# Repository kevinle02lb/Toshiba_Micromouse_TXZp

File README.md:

<div align="center">

# 🐭 Toshiba Micromouse

**Autonomous 16×16 Maze-Solving Robot**  
*Register-level firmware on Arm Cortex-M4*

</div>

---

## Overview

Micromouse is a classic robotics competition: an autonomous palm-sized robot explores a 16×16 grid maze, maps the walls, solves for the center, and then races back through the fastest route it discovered.

This project implements the entire stack from scratch — custom 4-layer PCB, mechanical chassis, and register-level firmware — with no reliance on external HAL libraries.

---

## Platform

<div align="center">

### **Toshiba TMPM4KNF10AFG** — Arm Cortex-M4 with FPU

</div>

The TMPM4KNF10AFG comes from the **[M4K Group](https://toshiba.semicon-storage.com/us/semiconductor/product/microcontrollers/txz4aplus-series/m4k-group.html)** of Toshiba's **[TXZ+™4A Series](https://toshiba.semicon-storage.com/us/semiconductor/product/microcontrollers/txz4aplus-series.html)** — 160 MHz Arm Cortex-M4 microcontrollers built for motor and inverter control. It pairs a fast floating-point core with dedicated on-chip hardware for driving motors, reading encoders, and sampling analog sensors, and is used across industrial and consumer motion systems such as BLDC/PMSM drives, HVAC compressors, power tools, and factory automation — with IEC 60730 self-diagnosis support for appliance functional safety.

| Capability | Role in this build |
|-----------|--------------------|
| Cortex-M4 @ 160 MHz + FPU | Navigation, PID, and flood-fill maze solving |
| On-chip motor & encoder hardware | Wheel feedback and PPG-generated motor PWM |
| High-speed analog sensing | IR wall detection |

The same silicon built for industrial three-phase drives runs a smaller-scale problem here — a 1 kHz closed-loop PID over two brushed DC gear-motors — with dedicated hardware handling encoder counting and motor PWM so the CPU stays free for navigation and flood-fill maze solving.

---

## Built With

<div align="center">

|  |  |  |  |  |
|:---:|:---:|:---:|:---:|:---:|
| **Arm Cortex-M4** | **Keil µVision** | **KiCad** | **Fusion 360** | **Git** |
| Register-level C | IDE / Build / Flash | 4-layer PCB | Chassis CAD | Version Control |

</div>

---

## Architecture Highlights

- **Flood-fill maze solver** — pure logic, zero hardware coupling
- **1 kHz per-wheel PID** speed control
- **Fully hand-written HAL** from datasheets, no external libraries
- **Relative-move navigation** — turn error never compounds across a run
- **Custom 4-layer PCB** with integrated motor drivers & IR sensors

---

## Gallery

<div align="center">

 &nbsp;&nbsp; 

*Custom PCB and test maze run*

<br>

*Fusion 360 render of the full mechanical assembly*

</div>

---

## Documentation
 
| Path | Contents |
|------|----------|
| [`src/README.md`](src/README.md) | Firmware architecture, control loops, pin map, timer config |
| [`pcb/README.md`](pcb/README.md) | Board specs, layout, schematic, component list |
| [`docs/README.md`](docs/README.md) | Docs index — assets, evidence, and analysis tooling |
| [`docs/evidence/README.md`](docs/evidence/README.md) | Module-test checklist and captured evidence |

---

## Quick Start

```text
IDE:     Keil µVision
Target:  TMPM4KNF10AFG (Arm Cortex-M4)
Debug:   CMSIS-DAP
Flash:   512 KB on-chip
```

---

<div align="center">

**Kevin Le** &nbsp;•&nbsp; 2026 &nbsp;•&nbsp;
</div>

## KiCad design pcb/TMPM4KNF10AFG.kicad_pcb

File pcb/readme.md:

<div align="center">

# Micromouse PCB

**Custom 4-Layer Control Board**  
*Integrated MCU, motor drivers, and IR sensing*

</div>

---

## Overview

The mainboard is a custom 4-layer PCB designed in KiCad that carries the full electronics stack on a single micromouse-sized board: the microcontroller, dual motor drivers, four IR wall sensors, and the power and debug interface.

---

## Board Specs

| Spec | Detail |
|------|--------|
| Layers | 4-layer |
| MCU | Toshiba TMPM4KNF10AFG (Cortex-M4F) |
| Motor drivers | 2 × TB67H450AFNG H-bridge |
| Sensing | 4 × IR emitter / receiver pairs |
| Debug | CMSIS-DAP (SWD) via TXB0104 level shifter |
| Supply | 5 V |

---

## Layout

<div align="center">

*Copper layers and component placement*

</div>

---

## Key Components

| Component | Part | Role |
|-----------|------|------|
| MCU | TMPM4KNF10AFG | Cortex-M4F — control & sensing |
| Motor driver | TB67H450AFNG ×2 | Brushed DC H-bridge, PWM speed control |
| Motors | Pololu #5211 N20 30:1 | Drive, with quadrature encoders |
| IR sensing | IR LED + phototransistor ×4 | Wall detection via ADC |
| Level shifter | TXB0104 | 5 V ↔ 3.3 V for SWD debug |

---

## Schematic

The full schematic is available as a PDF:

[View schematic (PDF)](Schematic.pdf)

---

## Files

| File | Contents |
|------|----------|
| `*.kicad_sch` | Schematic source |
| `*.kicad_pcb` | Board layout source |
| `gerbers/` | Fabrication outputs |

---

<div align="center">

[← Back to main README](../README.md)

</div>

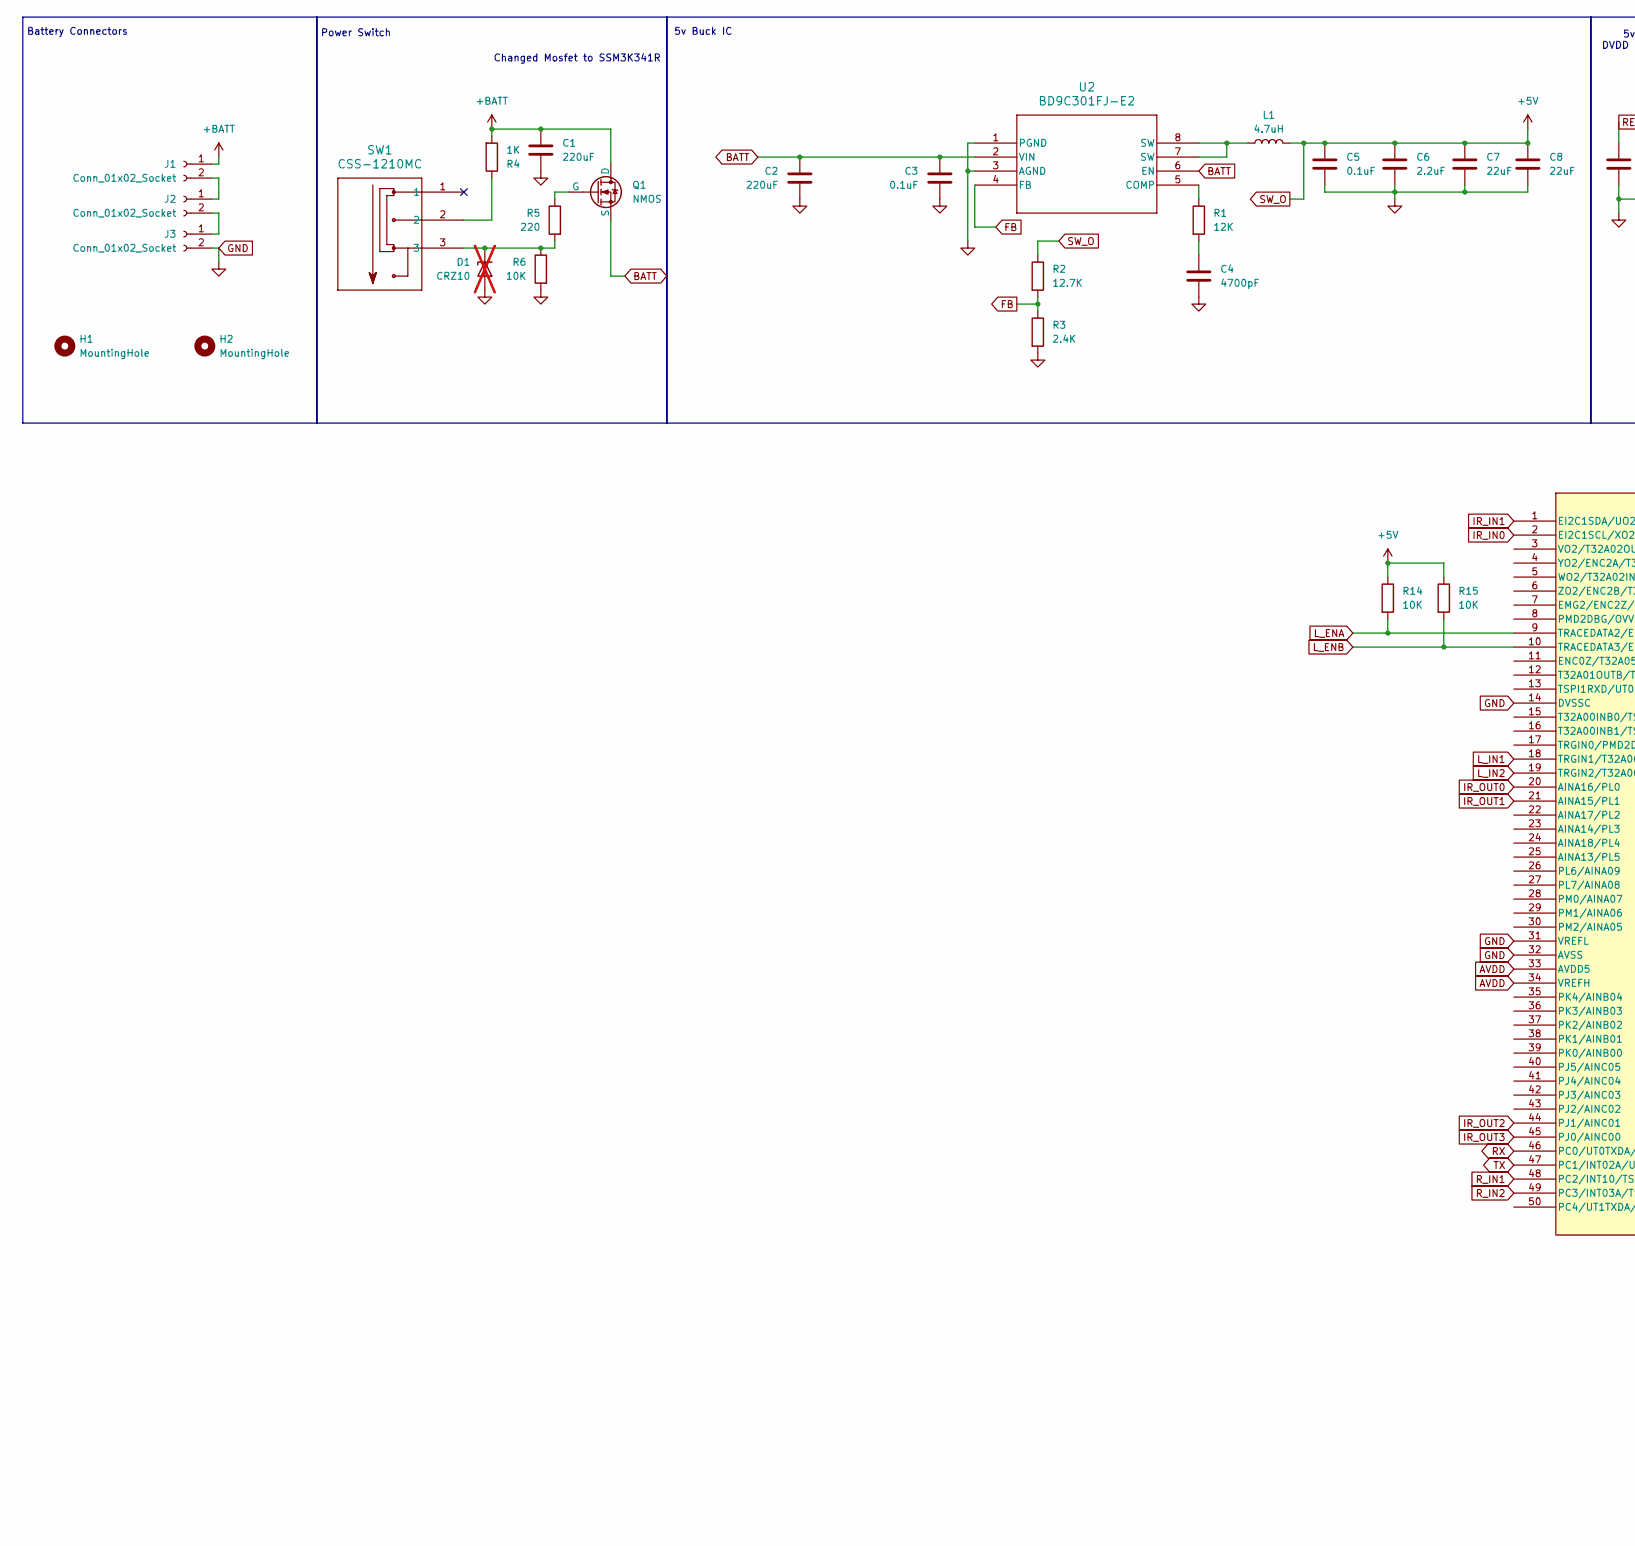
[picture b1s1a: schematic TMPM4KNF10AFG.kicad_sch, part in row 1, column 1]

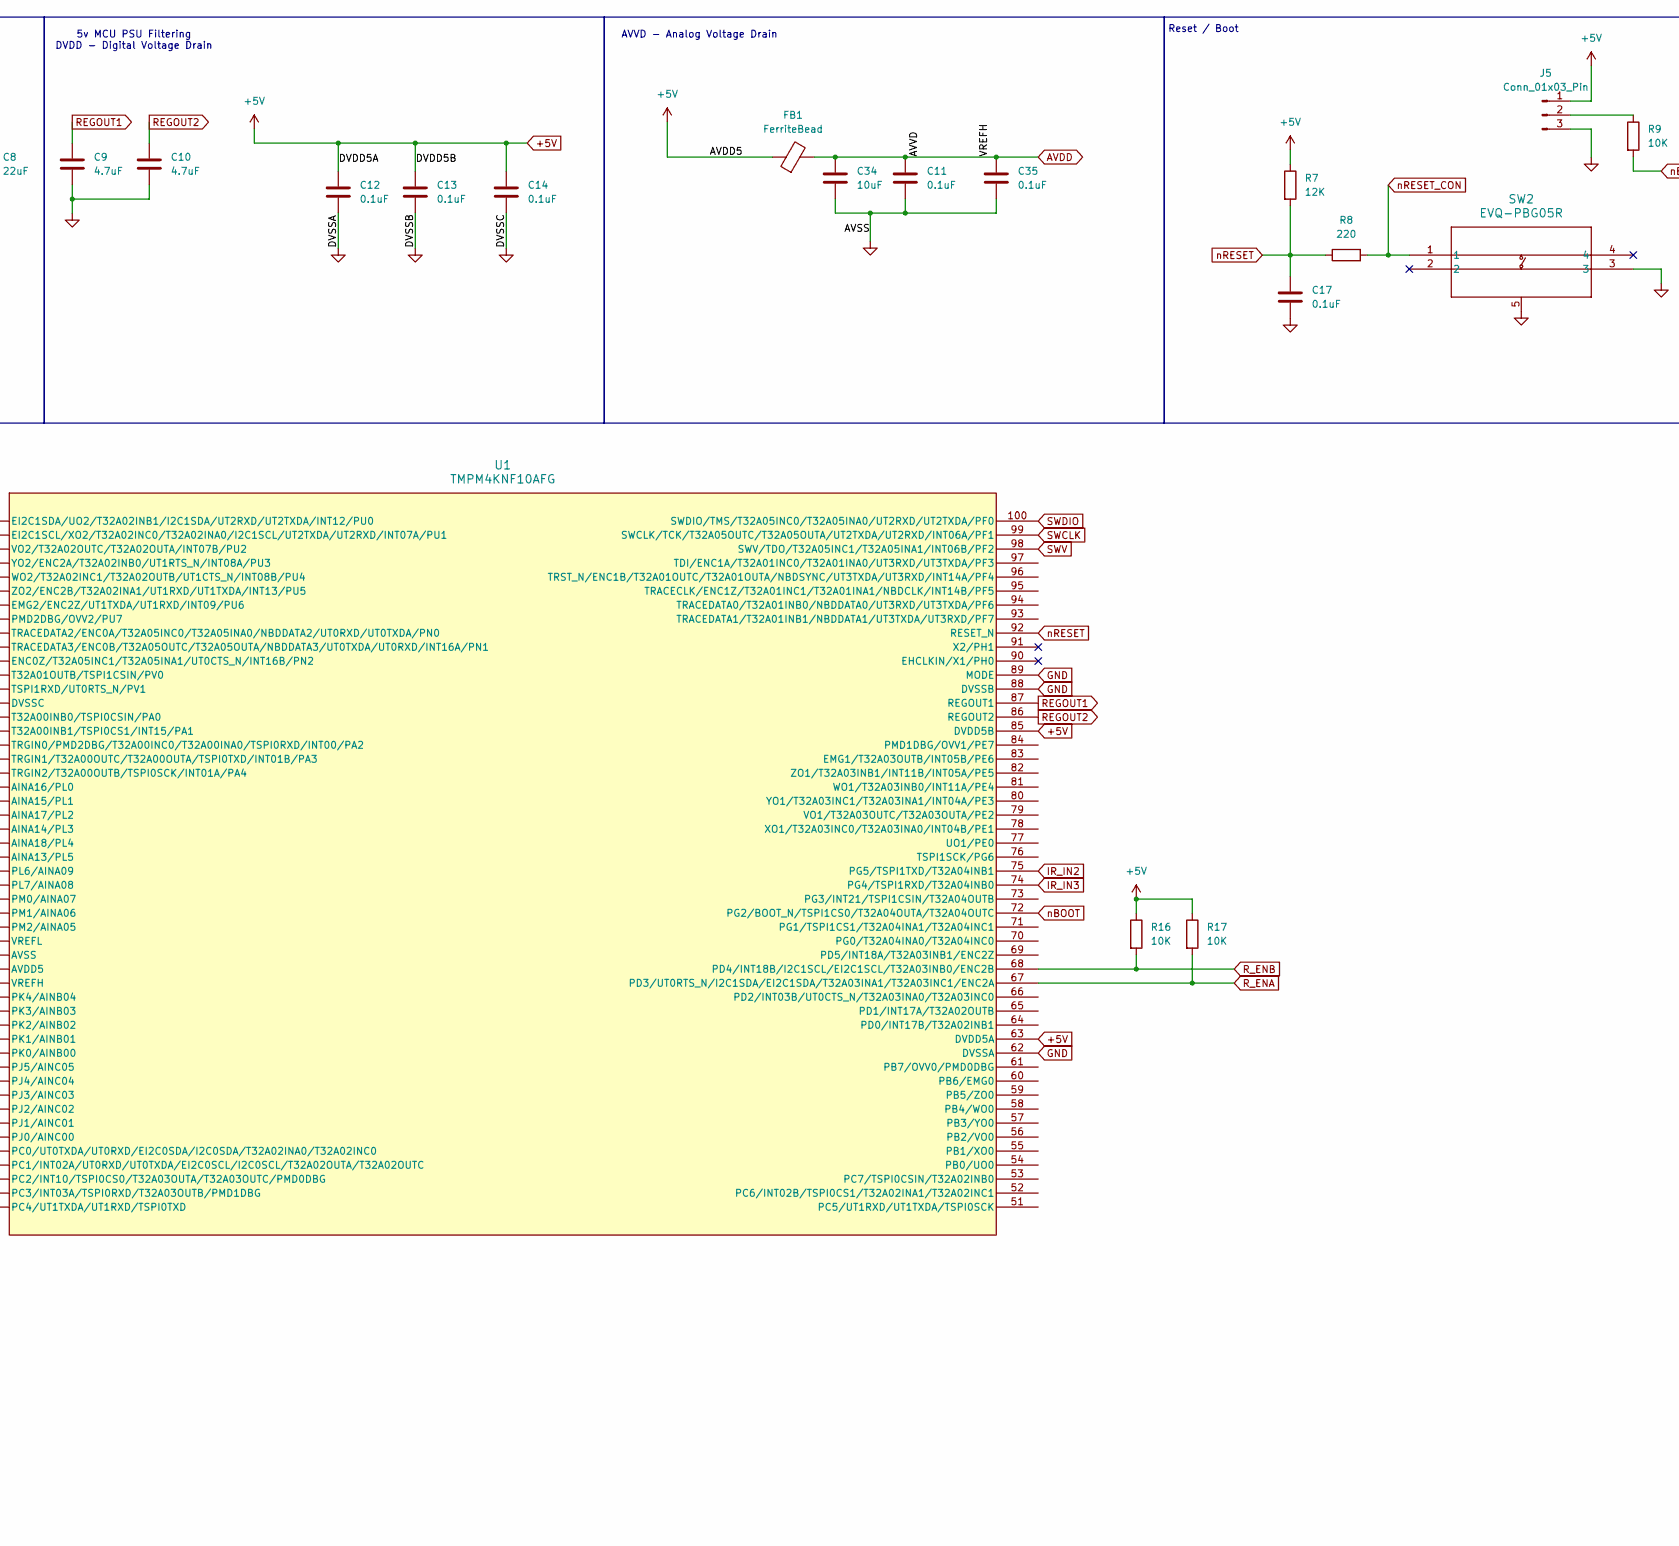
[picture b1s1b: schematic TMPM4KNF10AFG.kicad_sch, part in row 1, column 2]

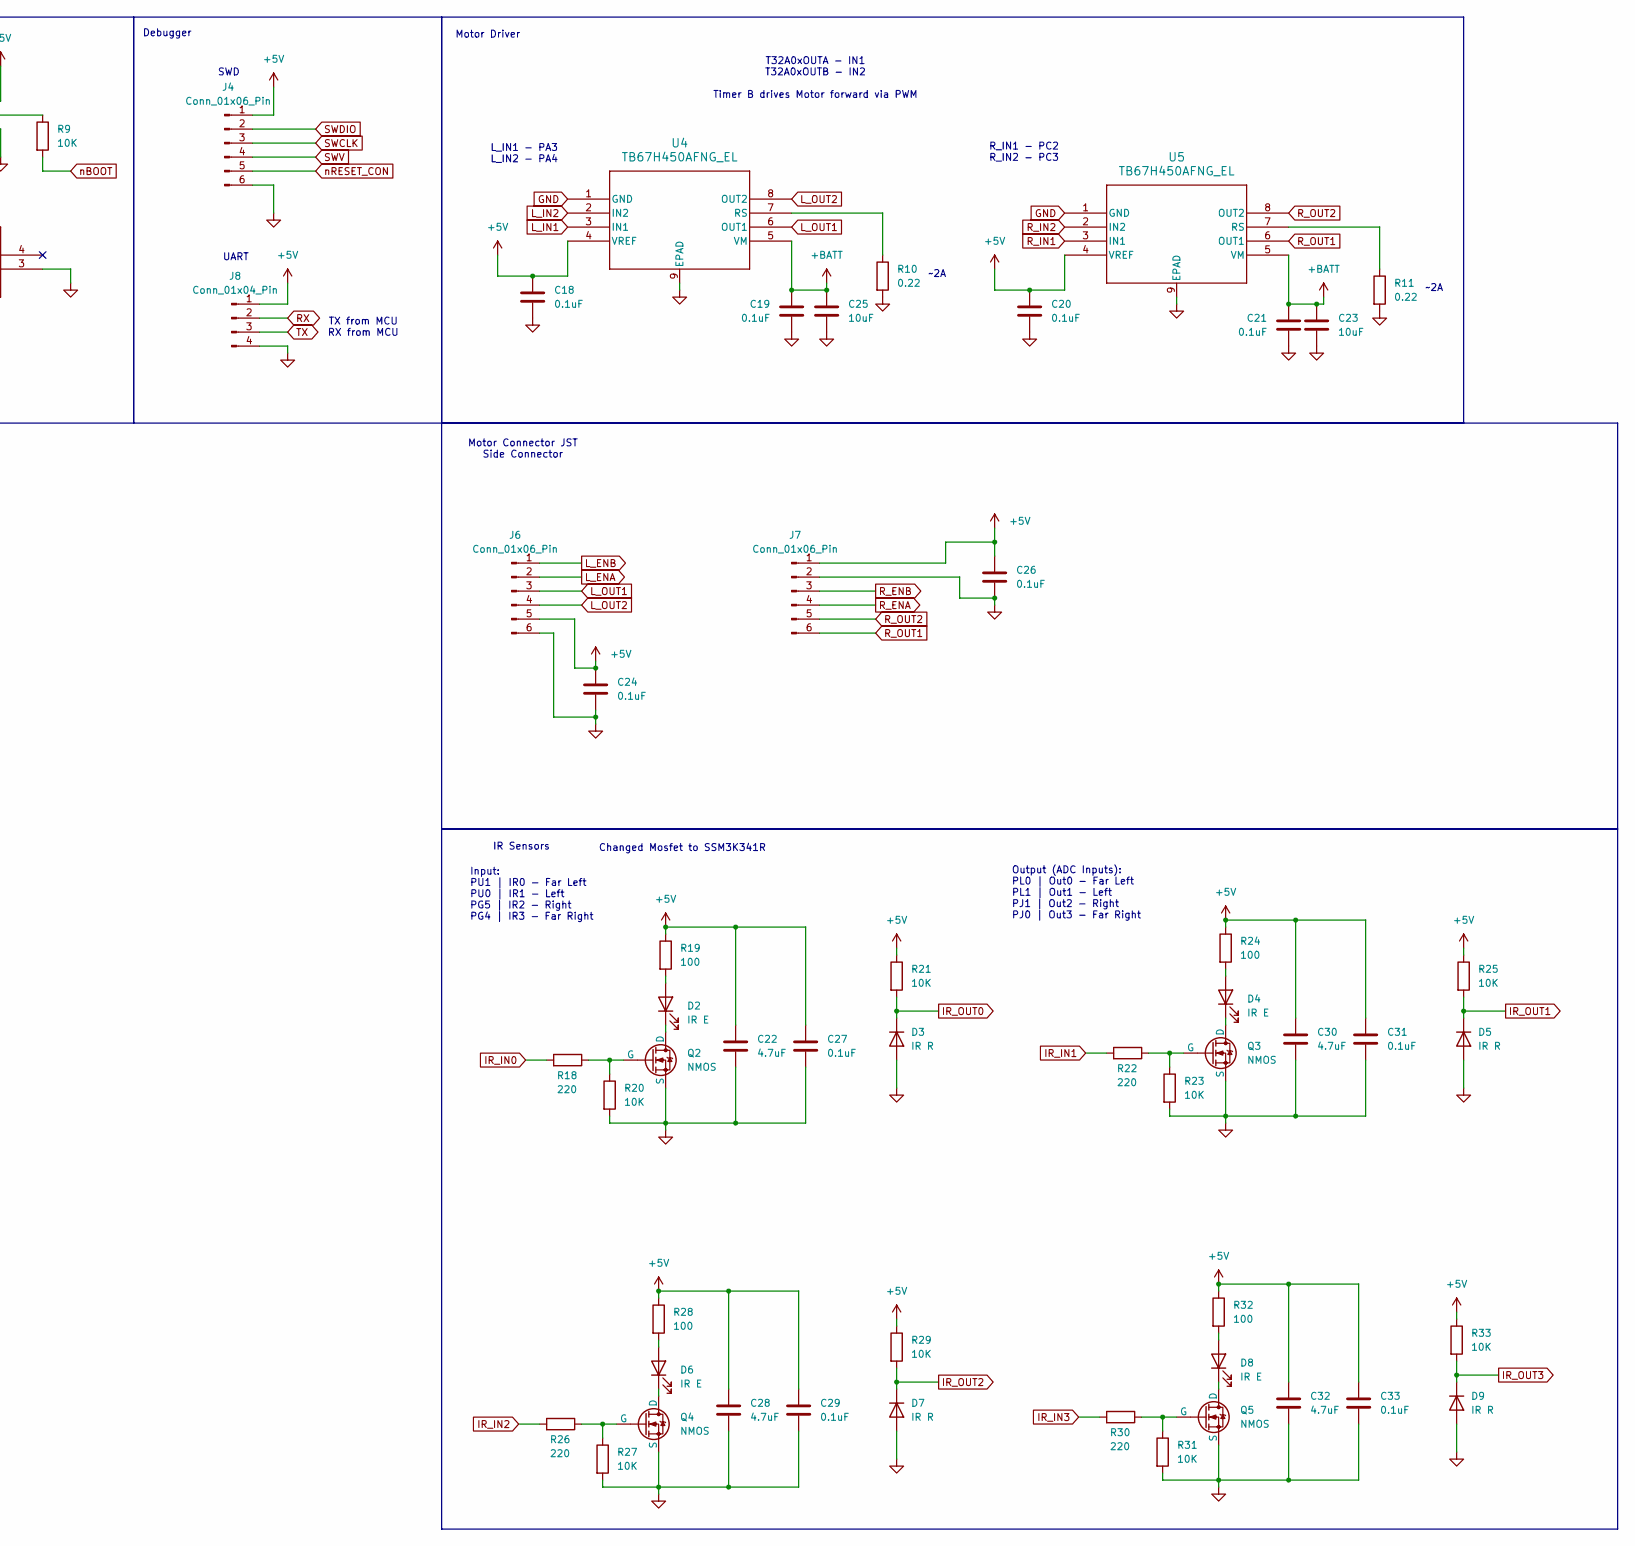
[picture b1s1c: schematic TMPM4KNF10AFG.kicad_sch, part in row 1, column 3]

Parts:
C1, C2: 220uF; CAP_20SVPG220M
C3, C5, C11, C12, C13, C14, C17, C18, C19, C20, C21, C24, C26, C27, C29, C31, C33, C35: 0.1uF; C_0805_2012Metric_Pad1.18x1.45mm_HandSolder
C4: 4700pF; C_0805_2012Metric_Pad1.18x1.45mm_HandSolder
C6: 2.2uF; C_0805_2012Metric_Pad1.18x1.45mm_HandSolder
C7, C8: 22uF; C_0805_2012Metric_Pad1.18x1.45mm_HandSolder
C9, C10, C22, C28, C30, C32: 4.7uF; C_0805_2012Metric_Pad1.18x1.45mm_HandSolder
C23, C25, C34: 10uF; C_0805_2012Metric_Pad1.18x1.45mm_HandSolder
D1: CRZ10; D_SOD-123F; not fitted
D2, D4, D6, D8: IR E; LED_D5.0mm_Horizontal_O1.27mm_Z3.0mm_Clear
D3, D5, D7, D9: IR R; LED_D5.0mm_Horizontal_O1.27mm_Z3.0mm_IRBlack
FB1: FerriteBead; L_0805_2012Metric_Pad1.05x1.20mm_HandSolder
H1, H2: MountingHole; MountingHole_3.2mm_M3
J1, J2, J3: Conn_01x02_Socket; JST_PH_S2B-PH-K_1x02_P2.00mm_Horizontal
J4: Conn_01x06_Pin; PinHeader_1x06_P2.54mm_Vertical
J5: Conn_01x03_Pin; PinHeader_1x03_P2.54mm_Vertical
J6, J7: Conn_01x06_Pin; PAD_01x06_2.54mm
J8: Conn_01x04_Pin; PinHeader_1x04_P2.54mm_Vertical
L1: 4.7uH; IND_1217AS-H-4R7N=P3
Q1, Q2, Q3, Q4, Q5: NMOS; SOT-23F_TOS-M
R1, R7: 12K; R_0805_2012Metric_Pad1.20x1.40mm_HandSolder
R2: 12.7K; R_0805_2012Metric_Pad1.20x1.40mm_HandSolder
R3: 2.4K; R_0805_2012Metric_Pad1.20x1.40mm_HandSolder
R4: 1K; R_0805_2012Metric_Pad1.20x1.40mm_HandSolder
R5, R8, R18, R22, R26, R30: 220; R_0805_2012Metric_Pad1.20x1.40mm_HandSolder
R6, R9, R14, R15, R16, R17, R20, R21, R23, R25, R27, R29, R31, R33: 10K; R_0805_2012Metric_Pad1.20x1.40mm_HandSolder
R10, R11: 0.22; R_0805_2012Metric_Pad1.20x1.40mm_HandSolder
R19, R24, R28, R32: 100; R_0805_2012Metric_Pad1.20x1.40mm_HandSolder
SW1: CSS-1210MC; SW3_CSS-1210MC_NDC
SW2: EVQ-PBG05R; EVQ-PBG05R_PAN
U1: TMPM4KNF10AFG; P-LQFP100-1414-0p50-002_TOS
U2: BD9C301FJ-E2; SOP-J8_ROM
U4, U5: TB67H450AFNG_EL; P-HSOP8-0405-1.27-002_TOS

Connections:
+5V: C5.1, C6.1, C7.1, C8.1, C12.1, C13.1, C14.1, C18.1, C20.1, C22.1, C24.1, C26.1, C27.1, C28.1, C29.1, C30.1, C31.1, C32.1, C33.1, FB1.1, J4.1, J5.1, J6.5, J7.1, J8.1, L1.2, R2.1, R7.1, R14.1, R15.1, R16.1, R17.1, R19.1, R21.1, R24.1, R25.1, R28.1, R29.1, R32.1, R33.1, U1.63 (DVDD5A), U1.85 (DVDD5B), U4.4 (VREF), U5.4 (VREF)
+BATT: C1.1, C19.1, C21.1, C23.1, C25.1, J1.1, Q1.1 (D), R4.2, U4.5 (VM), U5.5 (VM)
AVDD: C11.1, C34.1, C35.1, FB1.2, U1.33 (AVDD5), U1.34 (VREFH)
BATT: C2.1, C3.1, Q1.3 (S), U2.2 (VIN), U2.6 (EN)
FB: R2.2, R3.1, U2.4 (FB)
GND: C1.2, C2.2, C3.2, C4.2, C5.2, C6.2, C7.2, C8.2, C9.2, C10.2, C11.2, C12.2, C13.2, C14.2, C17.2, C18.2, C19.2, C20.2, C21.2, C22.2, C23.2, C24.2, C25.2, C26.2, C27.2, C28.2, C29.2, C30.2, C31.2, C32.2, C33.2, C34.2, C35.2, D1.2 (A), D3.2 (A), D5.2 (A), D7.2 (A), D9.2 (A), J3.2, J4.6, J5.3, J6.6, J7.2, J8.4, Q2.3 (S), Q3.3 (S), Q4.3 (S), Q5.3 (S), R3.2, R6.2, R10.2, R11.2, R20.2, R23.2, R27.2, R31.2, SW2.3, SW2.5, U1.14 (DVSSC), U1.31 (VREFL), U1.32 (AVSS), U1.62 (DVSSA), U1.88 (DVSSB), U1.89 (MODE), U2.1 (PGND), U2.3 (AGND), U4.1 (GND), U4.9 (EPAD), U5.1 (GND), U5.9 (EPAD)
IR_IN0: R18.2, U1.2 (EI2C1SCL/XO2/T32A02INC0/T32A02INA0/I2C1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)
IR_IN1: R22.2, U1.1 (EI2C1SDA/UO2/T32A02INB1/I2C1SDA/UT2RXD/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)
IR_IN2: R26.2, U1.75 (PG5/TSPI1TXD/T32A04INB1)
IR_IN3: R30.2, U1.74 (PG4/TSPI1RXD/T32A04INB0)
IR_OUT0: D3.1 (K), R21.2, U1.20 (AINA16/PL0)
IR_OUT1: D5.1 (K), R25.2, U1.21 (AINA15/PL1)
IR_OUT2: D7.1 (K), R29.2, U1.44 (PJ1/AINC01)
IR_OUT3: D9.1 (K), R33.2, U1.45 (PJ0/AINC00)
L_ENA: J6.2, R14.2, U1.9 (TRACEDATA2/ENC0A/T32A05INC0/T32A05INA0/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)
L_ENB: J6.1, R15.2, U1.10 (TRACEDATA3/ENC0B/T32A05OUTC/T32A05OUTA/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)
L_IN1: U1.18 (TRGIN1/T32A00OUTC/T32A00OUTA/TSPI0TXD/I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), U4.3 (IN1)
L_IN2: U1.19 (TRGIN2/T32A00OUTB/TSPI0SCK/INT01A/PA4), U4.2 (IN2)
L_OUT1: J6.3, U4.6 (OUT1)
L_OUT2: J6.4, U4.8 (OUT2)
unnamed: C4.1, R1.2
unnamed: D1.1 (K), R5.2, R6.1, SW1.3
unnamed: D2.2 (A), R19.2
unnamed: D2.1 (K), Q2.1 (D)
unnamed: D4.2 (A), R24.2
unnamed: D4.1 (K), Q3.1 (D)
unnamed: D6.2 (A), R28.2
unnamed: D6.1 (K), Q4.1 (D)
unnamed: D8.2 (A), R32.2
unnamed: D8.1 (K), Q5.1 (D)
unnamed: J1.2, J2.1
unnamed: J2.2, J3.1
unnamed: J5.2, R9.1
unnamed: L1.1, U2.7 (SW), U2.8 (SW)
unnamed: Q1.2 (G), R5.1
unnamed: Q2.2 (G), R18.1, R20.1
unnamed: Q3.2 (G), R22.1, R23.1
unnamed: Q4.2 (G), R26.1, R27.1
unnamed: Q5.2 (G), R30.1, R31.1
unnamed: R4.1, SW1.2
unnamed: R1.1, U2.5 (COMP)
unnamed: R10.1, U4.7 (RS)
unnamed: R11.1, U5.7 (RS)
REGOUT1: C9.1, U1.87 (REGOUT1)
REGOUT2: C10.1, U1.86 (REGOUT2)
RX: J8.2, U1.46 (PC0/UT0TXDA/UT0RXD/EI2C0SDA/I2C0SDA/T32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)
R_ENA: J7.4, R17.2, U1.67 (PD3/UT0RTS_N/I2C1SDA/EI2C1SDA/T32A03INA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)
R_ENB: J7.3, R16.2, U1.68 (PD4/INT18B/I2C1SCL/EI2C1SCL/T32A03INB0/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)
R_IN1: U1.48 (PC2/INT10/TSPI0CS0/T32A03OUTA/T32A03OUT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), U5.3 (IN1)
R_IN2: U1.49 (PC3/INT03A/TSPI0RXD/T32A03OUTB/PMD1DBG), U5.2 (IN2)
R_OUT1: J7.6, U5.6 (OUT1)
R_OUT2: J7.5, U5.8 (OUT2)
SWCLK: J4.3, U1.99 (SWCLK/TCK/T32A05OUTC/T32A05OUTA/UT2TXDA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)
SWDIO: J4.2, U1.100 (SWDIO/TMS/T32A05INC0/T32A05INA0/UT2RXD/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)
SWV: J4.4, U1.98 (SWV/TDO/T32A05INC1/T32A05INA1/INT06B/PF2)
TX: J8.3, U1.47 (PC1/INT02A/UT0RXD/UT0TXDA/EI2C0SCL/I2C0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)
nBOOT: R9.2, U1.72 (PG2/BOOT_N/TSPI1CS0/T32A04OUTA/T32A04OU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)
nRESET: C17.1, R7.2, R8.1, U1.92 (RESET_N)
nRESET_CON: J4.5, R8.2, SW2.1

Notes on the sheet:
Changed Mosfet to SSM3K341R
Battery Connectors
TX from MCU RX from MCU
R_IN1 - PC2 R_IN2 - PC3
Motor Connector JST Side Connector
UART
Output (ADC Inputs): PL0 | Out0 - Far Left PL1 | Out1 - Left PJ1 | Out2 - Right PJ0 | Out3 - Far Right
5v MCU PSU Filtering DVDD - Digital Voltage Drain
IR Sensors
T32A0xOUTA - IN1 T32A0xOUTB - IN2 Timer B drives Motor forward via PWM
Power Switch
Debugger
5v Buck IC
~2A
L_IN1 - PA3 L_IN2 - PA4
Motor Driver
SWD
AVVD - Analog Voltage Drain
Input: PU1 | IR0 - Far Left PU0 | IR1 - Left PG5 | IR2 - Right PG4 | IR3 - Far Right
Reset / Boot

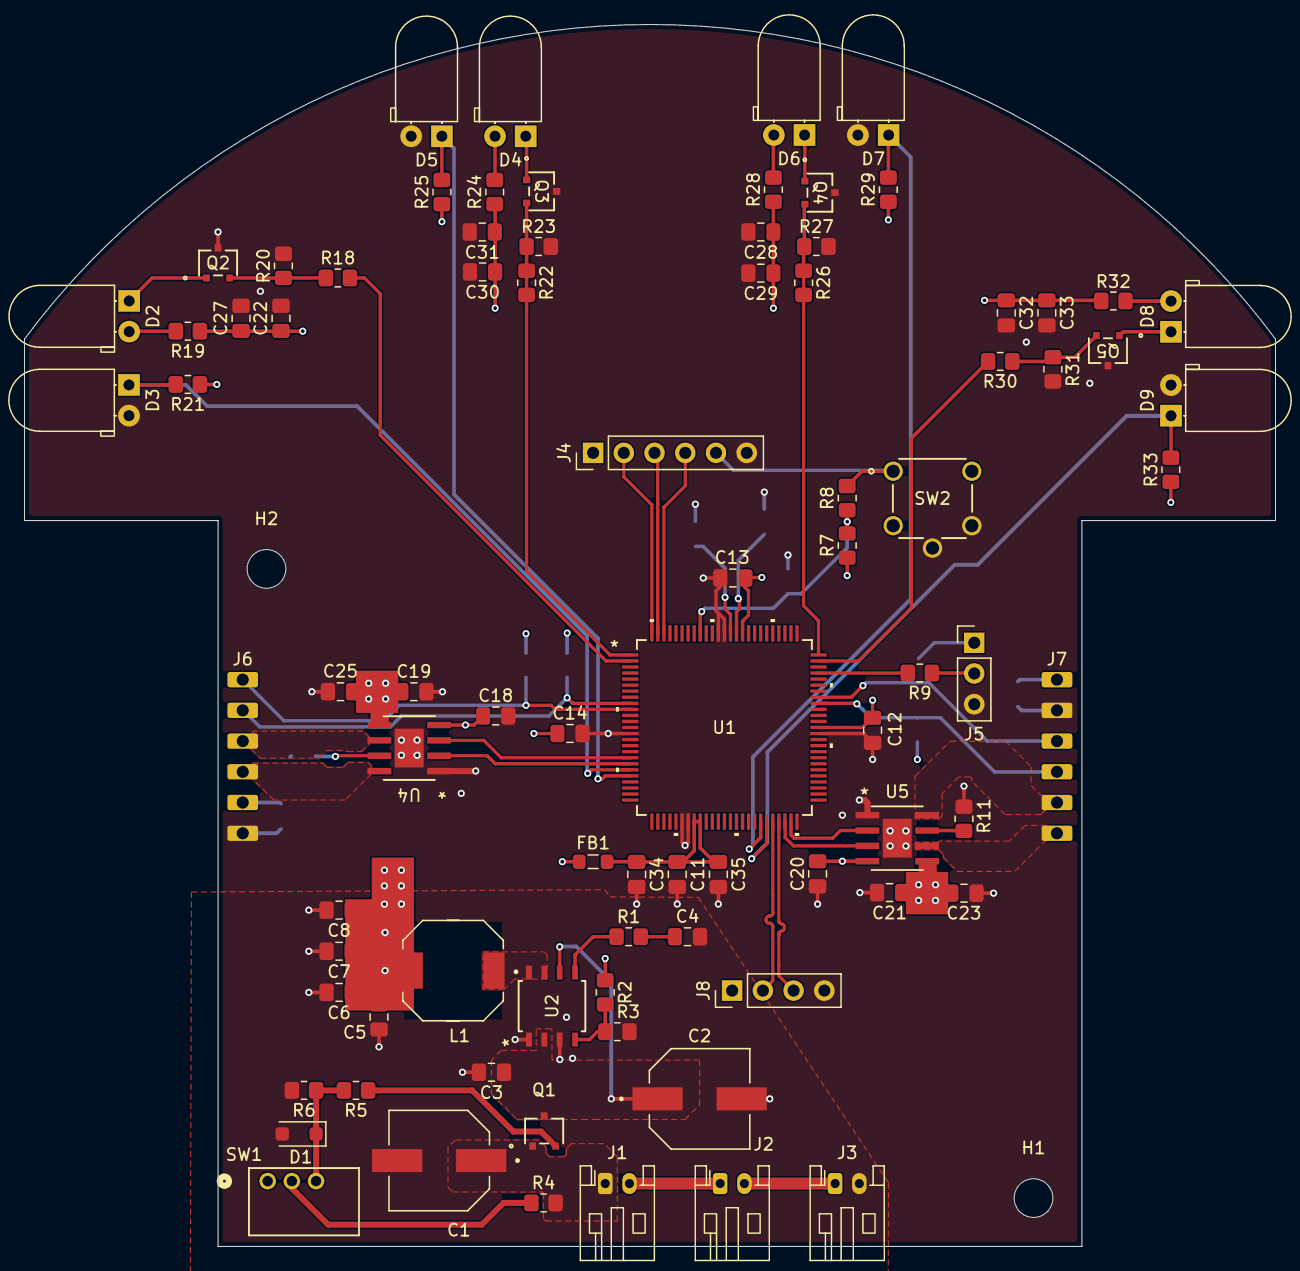
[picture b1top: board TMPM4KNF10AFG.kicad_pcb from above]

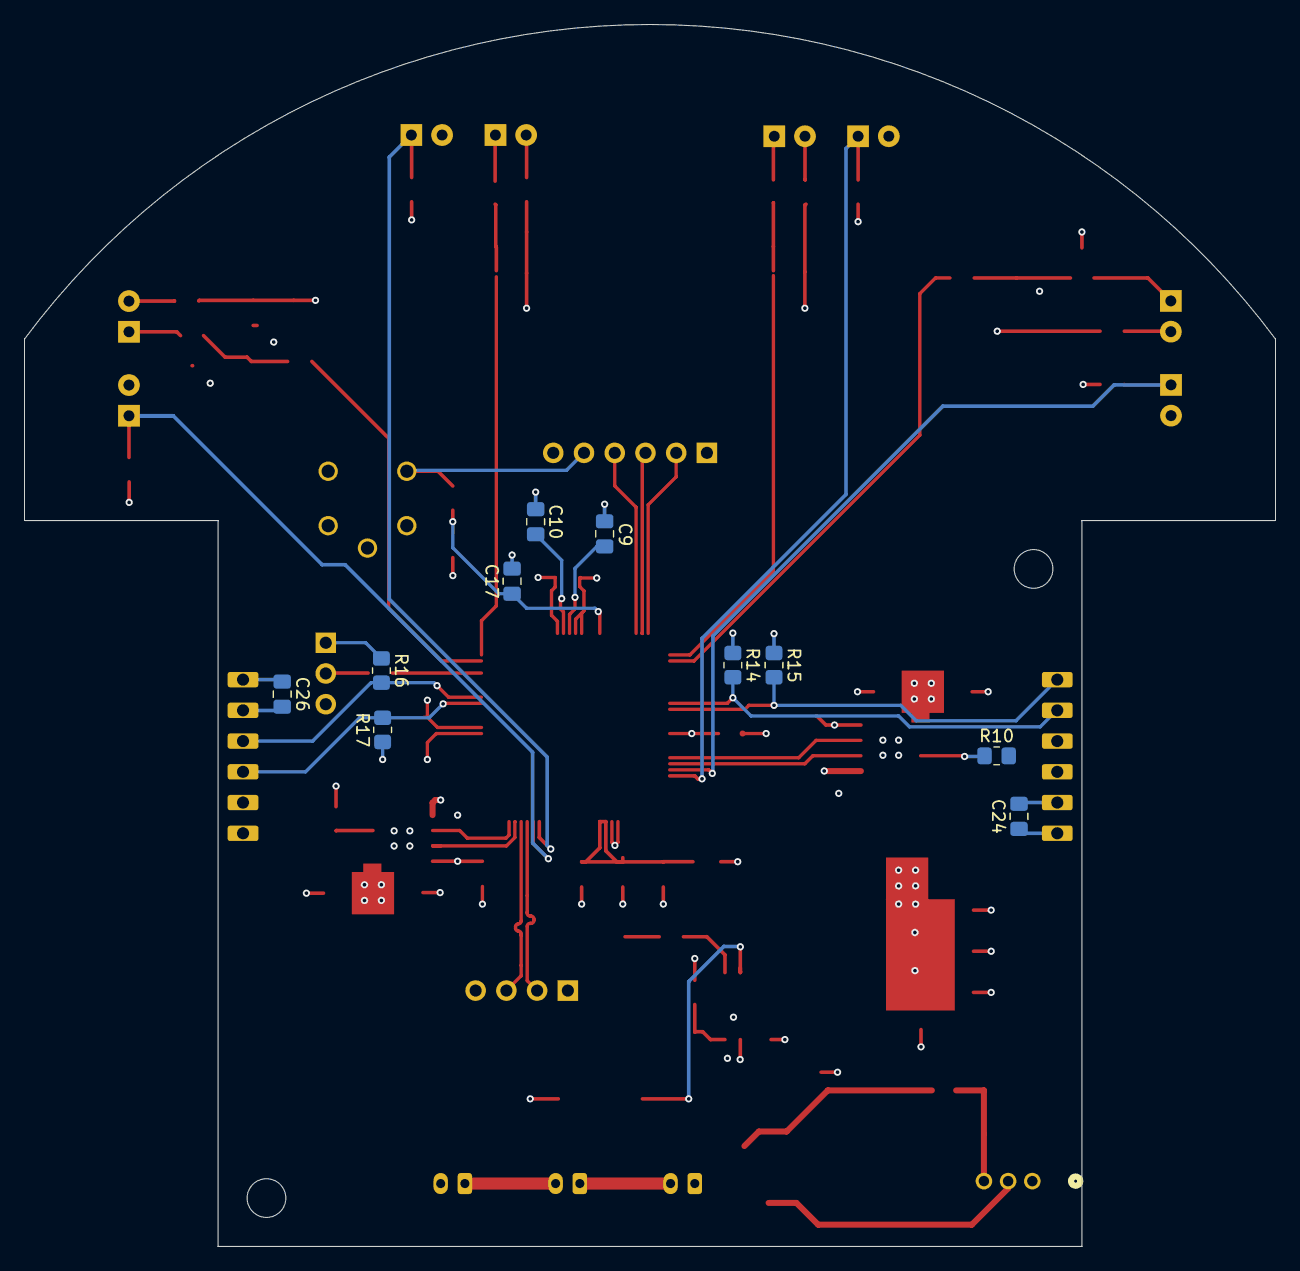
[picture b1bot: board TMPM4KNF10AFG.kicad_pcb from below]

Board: 4 copper layers, 103.4 x 101.0 mm, 96 parts (10 on the bottom side), 59 nets.

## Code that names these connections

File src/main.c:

/**
 ******************************************************************************
 * @file        main.c
 * @brief       Micromouse main firmware entry point
 * @version     V1.0.0
 * @date        05-05-2026
 *
 * @details
 *   Initializes the system clock and all modules, then runs the main control
 *   loop. Every 1 kHz tick (T32A1 interval timer) runs the full pipeline in
 *   fixed order:
 *
 *     Encoder_Update()   -> read quadrature counters, filter wheel speed
 *     Odometry_Update()  -> integrate pose (x, y, heading) from encoders
 *     Motion_Update()    -> PID speed loop, drive motor PWM (ALWAYS runs)
 *     Navigator_Update() -> non-blocking FSM: plan -> turn -> drive -> pause
 *
 *   Navigator is the top-level brain: it calls FloodFill (pure planner) for
 *   the next move, then sequences the physical turn/drive without ever
 *   blocking, so the PID loop above keeps running every tick.
 *
 *   Deployment calibration (must set before real runs):
 *   - IrSensor.c : ir_cal[] table (measured ADC-to-distance points)
 *   - Odometry.h : WHEELBASE_MM (measure wheel-center to wheel-center)
 *   - Encoder    : confirm forward motion yields INCREASING position
 *   - PID.h      : tune gains for CPS-scaled error
 *
 * ___________________________________________________________________________
 * Hardware:
 *   - MCU:     TMPM4KNF10AFG (ARM Cortex-M4, 5V, 160 MHz)
 *   - Motors:  TB67H450AFNG x2 + Pololu #5211 N20 30:1
 *   - Sensors: IR emitter/receiver pairs x4
 *   - Debug:   External CMSIS-DAP w/ Level Shifter (TXB0104)
 *
 * ___________________________________________________________________________
 * Pin Assignment:
 *   ┌─────────────────────────────────────────────────────────────┐
 *   │  PORT A  │ PA3  = 	 T32A00OUTA  (Left PWM IN1)            │
 *   │          │ PA4  = 	 T32A00OUTB  (Left PWM IN2)            │
 *   ├─────────────────────────────────────────────────────────────┤
 *   │  PORT C  │ PC2  = 	 T32A30OUTA  (Right PWM IN1)           │
 *   │          │ PC3  = 	 T32A30OUTB  (Right PWM IN2)           │
 *   ├─────────────────────────────────────────────────────────────┤
 *   │  PORT N  │ PN0  = 	 ENC0A  (Left encoder A)               │
 *   │          │ PN1  = 	 ENC0B  (Left encoder B)               │
 *   ├─────────────────────────────────────────────────────────────┤
 *   │  PORT D  │ PD3  = 	 ENC2A  (Right encoder A)              │
 *   │          │ PD4  = 	 ENC2B  (Right encoder B)              │
 *   ├─────────────────────────────────────────────────────────────┤
 *   │  PORT L  │ PL0  = 	 AINA16  (Far Left IR)                 │
 *   │          │ PL1  = 	 AINA15  (Left IR)                     │
 *   ├─────────────────────────────────────────────────────────────┤
 *   │  PORT J  │ PJ0  =     AINC00  (Far Right IR)                │
 *   │          │ PJ1  = 	 AINC01  (Right IR)                    │
 *   ├─────────────────────────────────────────────────────────────┤
 *   │  PORT U  │ PU0  =     Left IR Emitter                       │
 *   │          │ PU1  =     Far Left IR Emitter                   │
 *   ├─────────────────────────────────────────────────────────────┤
 *   │  PORT G  │ PG4  =     Far Right IR Emitter                  │
 *   │          │ PG5  =     Right IR Emitter                      │
 *   └─────────────────────────────────────────────────────────────┘
 *
 * ___________________________________________________________________________
 * Aliases (for quick reference):
 *   - PA3 = IN1, PA4 = IN2  (Left motor, T32A00OUTA/B)
 *   - PC2 = IN1, PC3 = IN2  (Right motor, T32A30OUTA/B)
 *   - PN0 = ENC0A, PN1 = ENC0B  (Left encoder)
 *   - PD3 = ENC2A, PD4 = ENC2B  (Right encoder)
 *   - PL0 = AINA16 (Far Left IR), PL1 = AINA15 (Left IR)
 *   - PJ1 = AINC01 (Right IR), PJ0 = AINC00 (Far Right IR)
 *   - PU1 = Far Left IR Emitter, PU0 = Left IR Emitter
 *   - PG5 = Right IR Emitter, PG4 = Far Right IR Emitter
 *
 * ___________________________________________________________________________
 * Notes:
 *   - MCU must be powered at 5V for ADC to function.
 *   - See TMPM4KNF10AFG datasheet section 7.2.
 *
 * ___________________________________________________________________________
 * References:
 *   - Product Info:  https://toshiba.semicon-storage.com/info/TXZP-PINFO-M4K(2)_en_20231225.pdf?did=70854
 *   - Datasheet:     https://toshiba.semicon-storage.com/info/TMPM4KNF10AFG_datasheet_en_20250516.pdf?did=155921&prodName=TMPM4KNF10AFG
 *
 * Copyright (c) [Kevin Le] 2026
 ******************************************************************************
 */


/* Inclusions */
#include "TMPM4KyA.h"
#include "system_TMPM4KyA.h"
#include "modules/Timebase.h"    // 1 kHz tick flag (T32A1)
#include "modules/Encoder.h"     // quadrature speed + position
#include "modules/Odometry.h"    // pose estimate (x, y, heading)
#include "modules/Motion.h"      // PID speed loop + motor drive
#include "modules/IrSensor.h"    // IR wall sensing (ADC + DMA)
#include "modules/FloodFill.h"   // pure maze planner (BFS)
#include "modules/Navigator.h"   // top-level motion sequencer FSM


void ModuleInit(void);




int main(void)
{
	SystemInit();								/* Initialize system clock and peripherals */
	ModuleInit();
	

	/* Control loop: fires once per 1 kHz tick. Order matters — each stage
	 * consumes the output of the one above it within the same tick.       */
	while (1)
	{
		if (Timebase_GetAndClear())     // true once per 1 ms tick
		{
			Encoder_Update();           // 1. read encoders, filter speed
			Odometry_Update();          // 2. update pose from encoders
			Motion_Update();            // 3. PID -> motor PWM (never blocks)
			Navigator_Update();         // 4. plan/turn/drive FSM step
		}
	}

	return 0;
}



/**
 * @brief  Initialize all modules in dependency order.
 * @note   Call once after SystemInit().
 *
 *   Each driver configures its own GPIO port internally, so no separate
 *   GPIO_Init() pass is needed. SysTick needs no init (stateless).
 *
 *   Order:
 *   1. Motion   -> Encoder + Motor (PWM T32A0/3, encoder ports) up first
 *   2. Odometry -> caches encoder position, so must follow Motion
 *   3. IR       -> DMAC + ADC + emitter ports; ADC uses SysTick_us (stateless)
 *   4. FloodFill-> planner; samples IR on first Plan(), so IR must precede it
 *   5. Navigator-> depends on FloodFill + Motion
 *   6. Timebase -> starts 1 kHz tick LAST
 */
void ModuleInit(void)
{
    Motion_Init();      // -> Encoder_Init() + Motor_Init()
    Odometry_Init();    // reads Encoder position
    IR_Init();          // -> DMAC_Init() + ADC_Init() + emitter ports
    FloodFill_Init();
    Navigator_Init();
    Timebase_Init();    // start tick last
}

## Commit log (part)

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2026-06-07 Finished DMA drivers. Need to finialize and organize ADC drivers
2026-06-07 Reformatted ADC & DMA drivers w/ AI Assistant
2026-06-07 Rewrote comments
2026-06-07 Reorganized/Reworded Driver files
2026-06-08 Finished T32A drivers for Main control loop system update rate
2026-06-08 Added IRQ handler logic and some fixes
2026-06-08 Implemented readme.md. Still work in Progress
2026-06-14 Worked on IR Sensor module. Need to finalize Distance calculations
2026-06-15 Implemnted IR module distance calculations
2026-06-16 Redid Encoder drivers & related modules for system coherence
2026-06-18 Implemented Encoder module
2026-06-19 Implemented some PID controller & renamed modules for readability
2026-06-20 Did PID module (WIP)
2026-06-22 Added docs folder and worked on integrated Motor & PID controls to Motion.c
2026-06-22 Fixed functions/formatting for Motion.c
2026-06-26 Odometry_Update Implemented
2026-06-27 Done Optometry Module
2026-06-28 Added turn left & right motion control functions for Motion.c
2026-06-28 Added 2 modules: Maze & FloodFill
